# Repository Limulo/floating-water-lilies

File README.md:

# README

**floating water lilies** WIP.

## Over Head Controlled lilies (silent lilies)

Le ninfee ricevono comandi da una stazione di controllo master e **non** sono pensate per comunicare l'un l'altra. In tale caso la singola ninfeaa deve montare:
* ricevitore di luce infrarossa (come il [TSOP](http://www.robot-italy.com/en/tsop2236-ir-receiver-modules-for-remote-control-systems.html));

Il sistema **OHC** invece deve avere uno o più:
* LED ad infrarossi o trasmettitore ad infrarossi.

## Autonomous Chatty Lilies (w/o OHC)

Le ninfee sono agenti autonomi con comportamenti prestabiliti dal codice e reagiscono agli stimoli esterni senza bisogno di direttiva dal OHC. La comunicazione deve avvenire in ambo le direzioni. Sarà necessaio quindi fornire ciascuna ninfea di:

* trasmettitore IR (uno o più)
* ricevitore IR (uno o più)

Risolvere eventuali problemi di _crosstalk_.

## Autonomous Chatty Lilies w/ OHC

Questo caso differisci di poco rispetto al precedente. Si tratta infatti dell'unione delle prime due casistiche.

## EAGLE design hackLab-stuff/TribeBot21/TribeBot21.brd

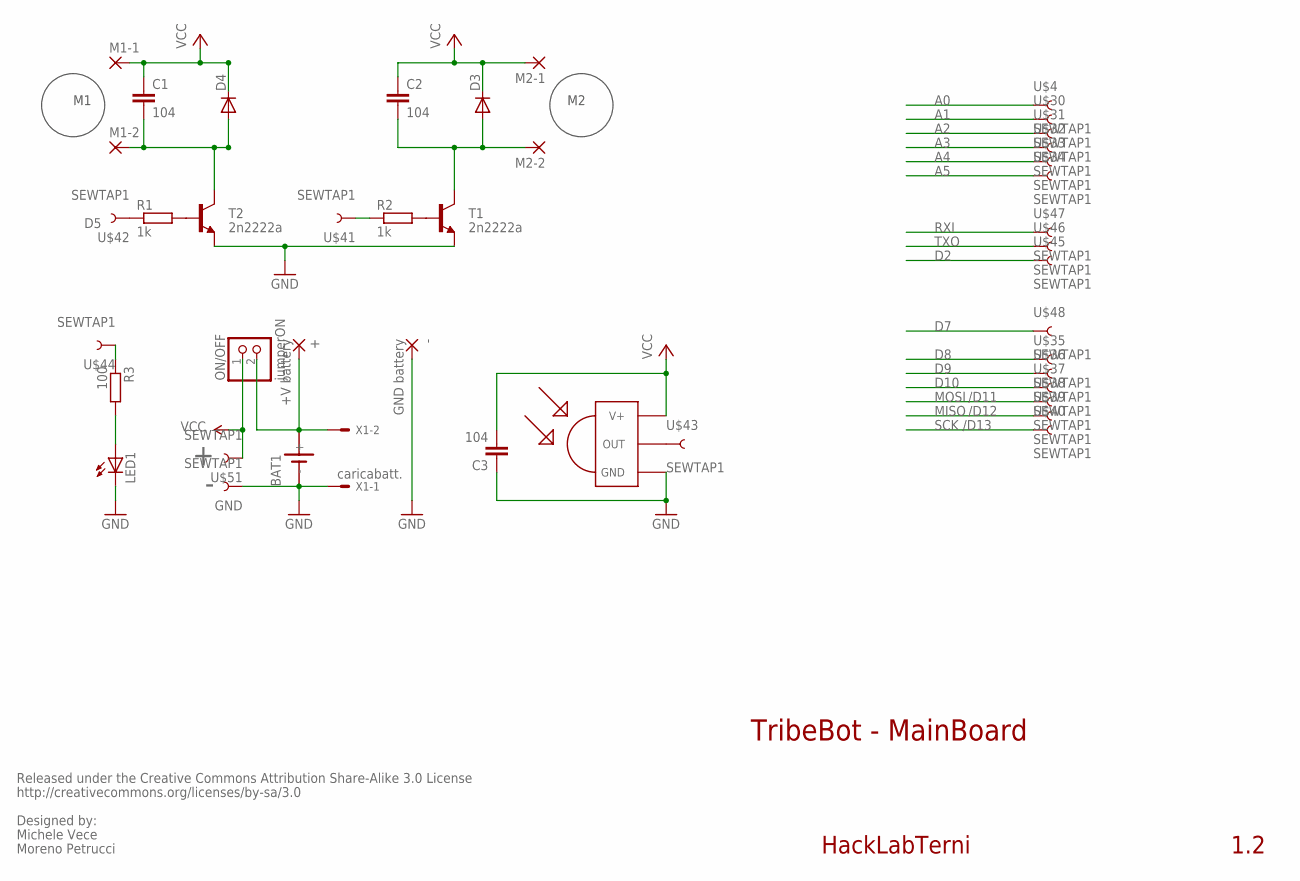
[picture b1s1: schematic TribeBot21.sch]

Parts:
+: +V battery; 2,15/1,0
-: GND battery; 2,15/1,0
BAT1: SN2032
C1, C2, C3: 104; C2.5-2
D3, D4: 1N4148DO35-7; DO35-7
GND: SEWTAP1; PETAL-LONG-1
LED1: LED_ELD260; LED_LD260
M1-1, M1-2, M2-1, M2-2: 1,6/0,8
ON/OFF: jumperON; 1X02
R1, R2: 1k; 0204/7
R3: 100; 0204/7
T1, T2: 2n2222a; TO-92
U$1: TSOP4838; TSOP18XX
U$4, U$30, U$31, U$32, U$33, U$34, U$35, U$36, U$37, U$38, U$39, U$40, U$41, U$42, U$43, U$44, U$45, U$46, U$47, U$48, U$51: SEWTAP1; PETAL-LONG-1
X1: caricabatt.; 22-23-2021

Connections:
A0: U$4.1
A1: U$30.1
A2: U$31.1
A3: U$32.1
A4: U$33.1
A5: U$34.1
D2: U$45.1
D7: U$48.1
D8: U$35.1
D9: U$36.1
D10: U$37.1
GND: -.1, BAT1.-, C3.1, GND.1, LED1.K (C), T1.1 (E), T2.1 (E), U$1.GND, X1.1
MISO: U$39.1
MOSI: U$38.1
unnamed: R1.2, T2.2 (B)
unnamed: R2.2, T1.2 (B)
unnamed: R1.1, U$42.1
unnamed: R2.1, U$41.1
unnamed: LED1.A, R3.2
unnamed: +.1, BAT1.+, ON/OFF.2, X1.2
unnamed: U$1.OUT, U$43.1
unnamed: C1.2, D4.A, M1-2.1, T2.3 (C)
unnamed: R3.1, U$44.1
unnamed: C2.2, D3.A, M2-2.1, T1.3 (C)
RXI: U$47.1
SCK: U$40.1
TXO: U$46.1
VCC: C1.1, C2.1, C3.2, D3.C, D4.C, M1-1.1, M2-1.1, ON/OFF.1, U$1.VCC (V+), U$51.1

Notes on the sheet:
TribeBot - MainBoard
HackLabTerni
/D11
/D12
/D13
Released under the Creative Commons Attribution Share-Alike 3.0 License
http://creativecommons.org/licenses/by-sa/3.0
Designed by:
Michele Vece
Moreno Petrucci
1.2

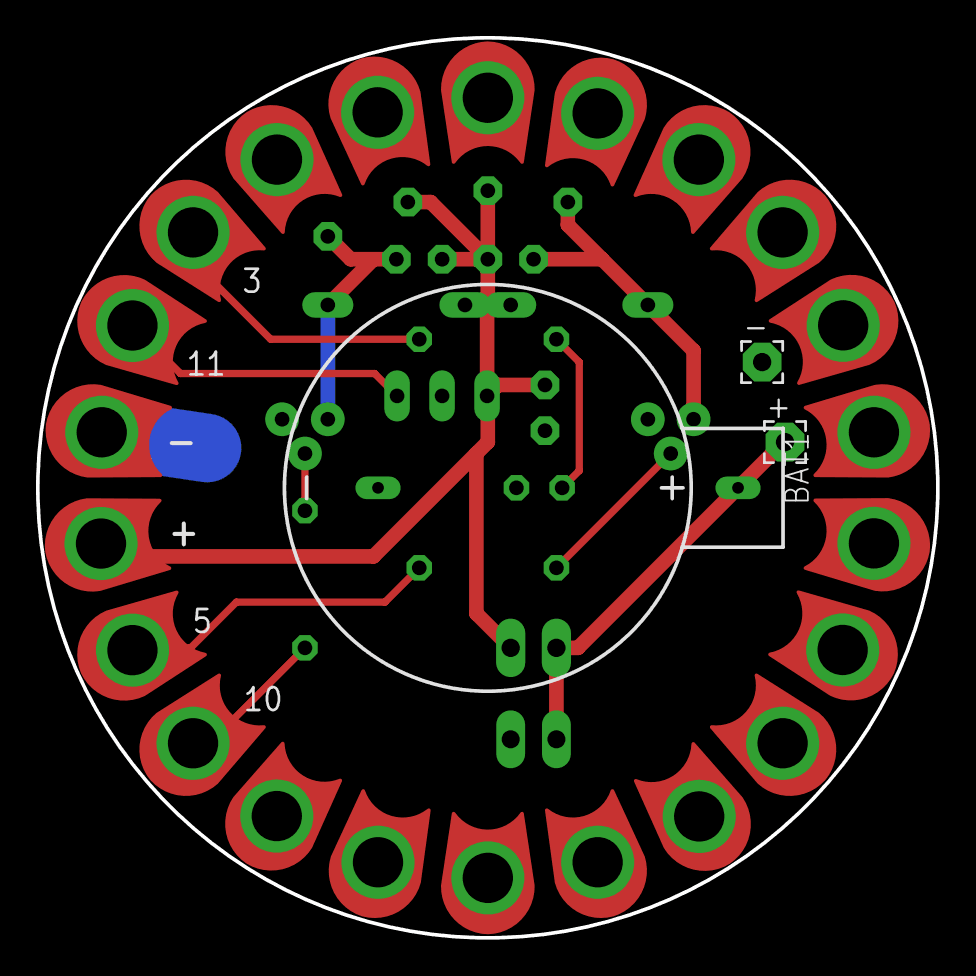
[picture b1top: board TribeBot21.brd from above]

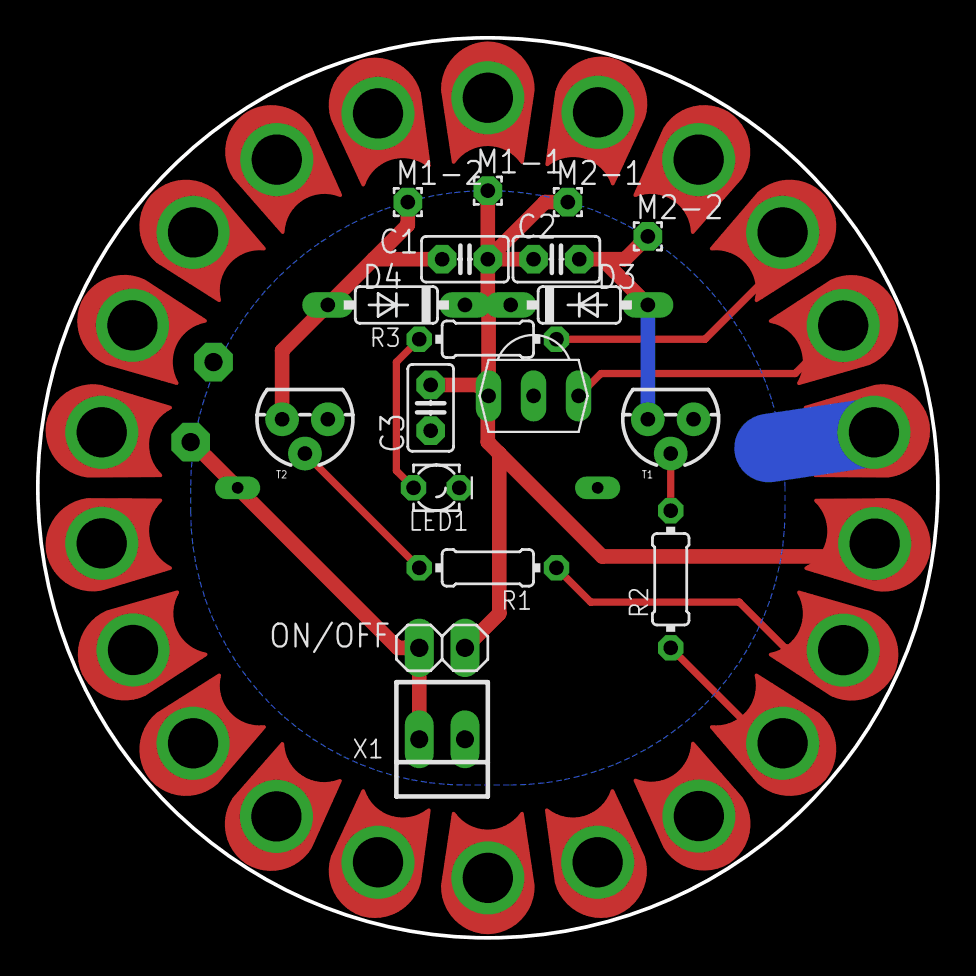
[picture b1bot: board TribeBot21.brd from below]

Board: 2 copper layers, 50.0 x 50.0 mm, 43 parts (18 on the bottom side), 12 nets.

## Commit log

2017-01-18 nuovo materiale in ninfee
2017-01-19 aggiornamenti README, aggiunta di docs, papers e datasheets
2017-01-20 wiki update
2017-01-27 aggiunti nuovi spunti e documenti pdf
2017-01-29 aggiunti nuovi documenti e modifiche al WIKI
2017-01-31 Gemma stuff and links in wiki.md
2017-01-31 typo
2017-01-31 info alimentazione gemma da pdf
2017-01-31 Lilypad info and links added
2017-02-04 aggiunti nuovi spunti al wiki
2017-02-04 ulteriori modifiche
2017-02-14 nuovi datasheet
2017-02-27 pdf e doc sull'uso del USBtyni programmer
2017-08-10 ultime aggiunte: pausa

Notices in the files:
parts and their libraries:
SparkFun-DiscreteSemi: Licensing: Creative Commons ShareAlike 4.0 International - https://creativecommons.org/licenses/by-sa/4.0
